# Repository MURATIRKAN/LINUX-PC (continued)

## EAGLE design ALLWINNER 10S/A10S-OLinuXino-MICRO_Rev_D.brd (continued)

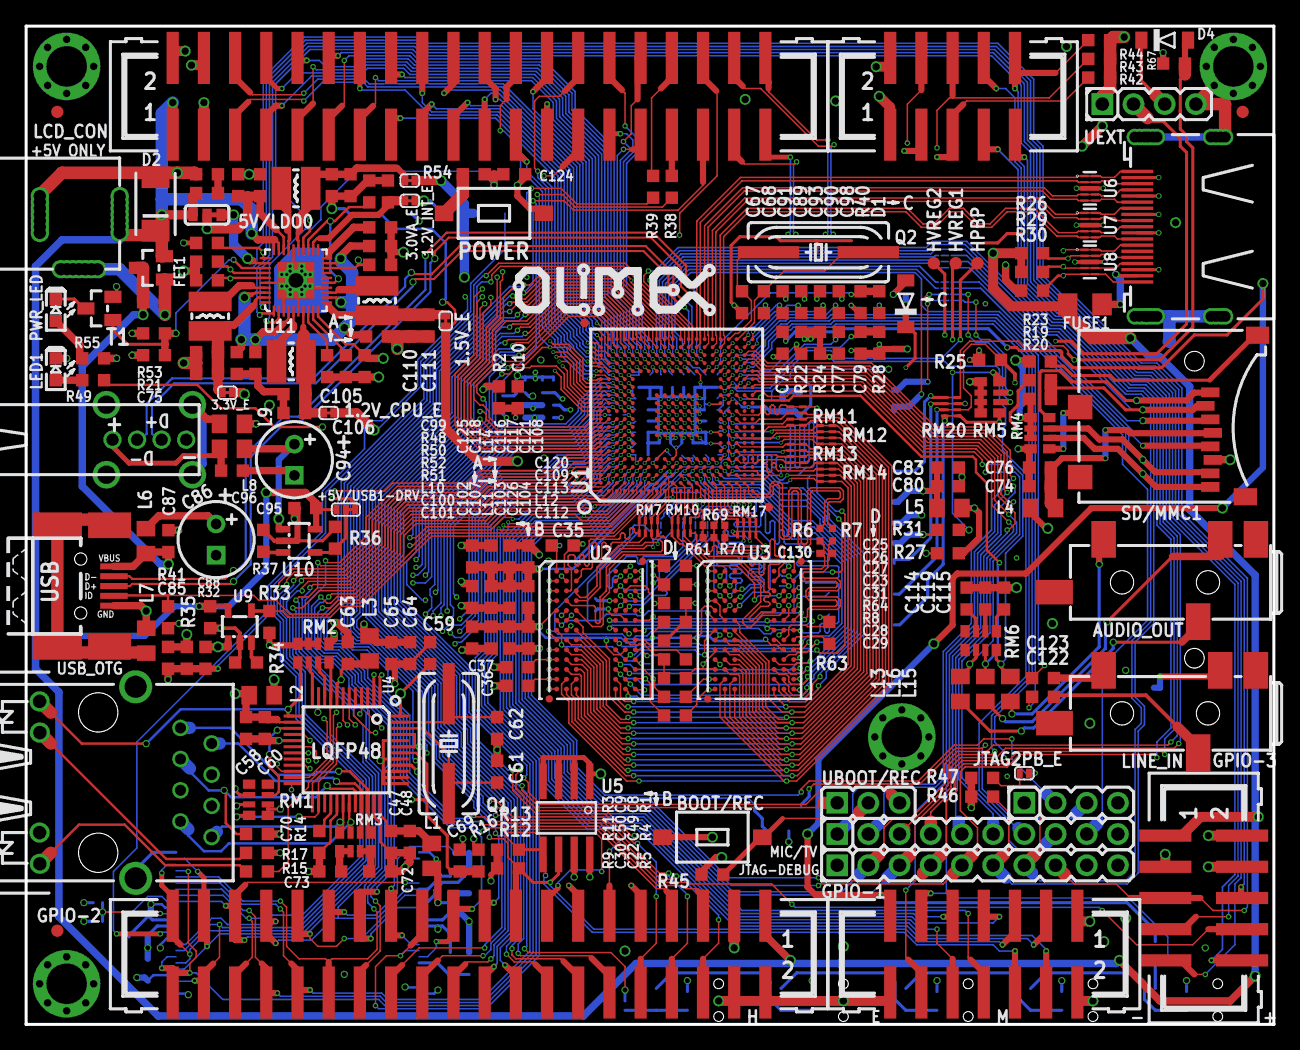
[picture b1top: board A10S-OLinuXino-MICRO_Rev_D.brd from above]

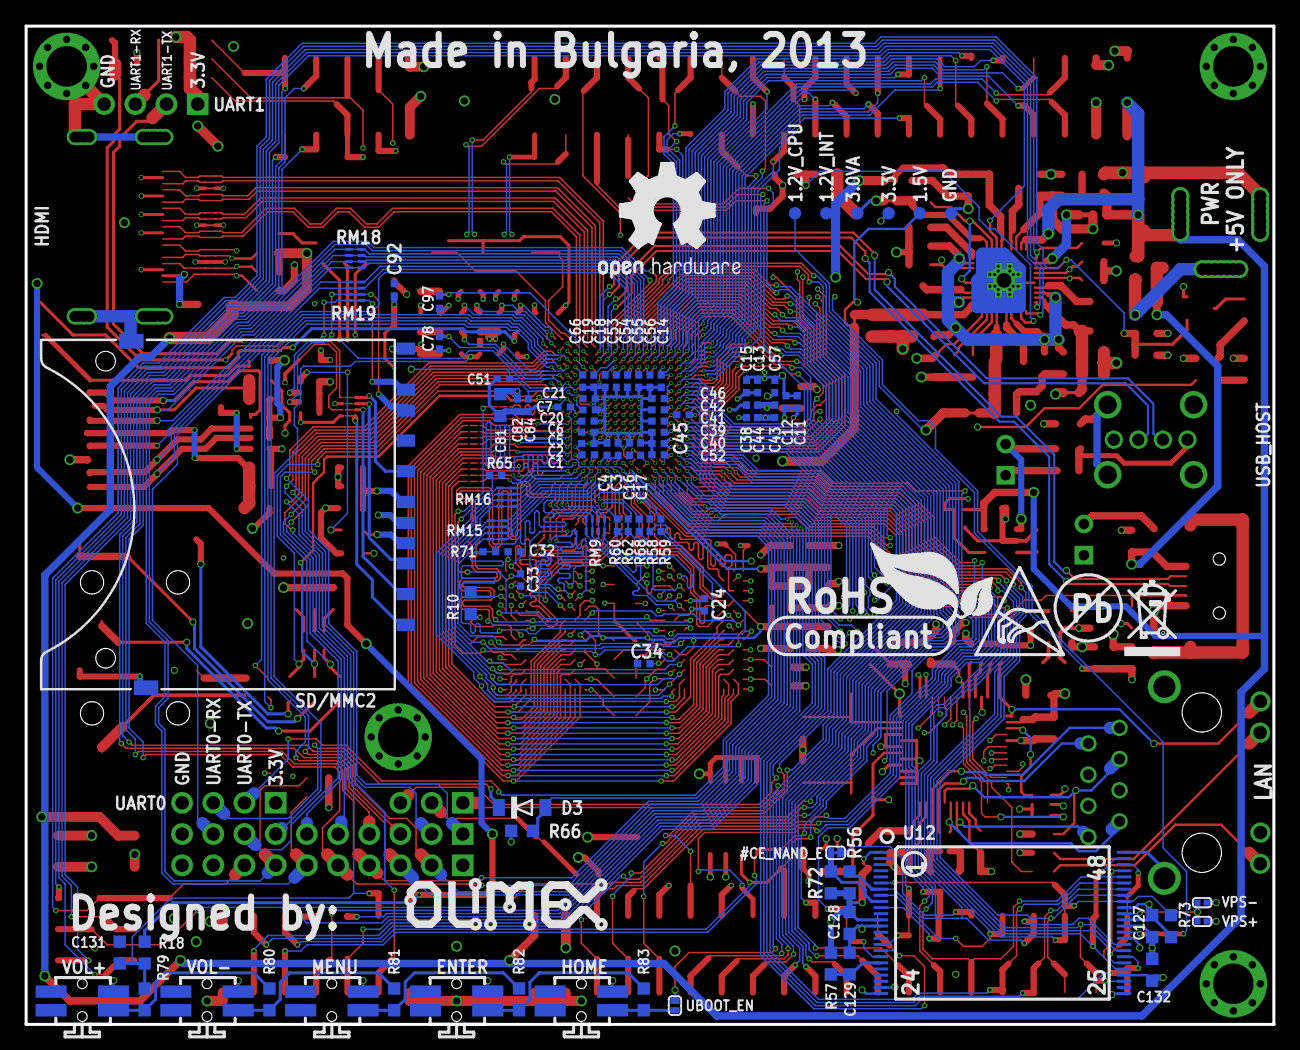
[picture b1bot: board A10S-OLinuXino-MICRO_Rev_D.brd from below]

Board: 4 copper layers, 101.6 x 81.3 mm, 325 parts (98 on the bottom side), 385 nets.

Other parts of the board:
U$5: LOGO-OPENHARDWARE_8X8
U$6, U$8: OLIMEX1_V
U$9: PB
U$10: ESD_SYMBOL
U$11: RECYCLE_BIN1/8
U$12: ROHS
